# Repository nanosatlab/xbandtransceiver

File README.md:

# **Description**

The subsystem is designed as a generic X-band front-end subsystem. It will have to communicate with an On-Board-Computer (OBC) using UART protocol, be powered from the spacecraft’s 12 V power bus and have a PC/104 daughter board form factor. It also has to ensure a downlink data rate of at least 10 Mbps from 5º over the horizon at a 550 km LEO orbit, and with a bit-error-rate (BER) of 10^-5.

The subsystem is formed by:	SDR <-> Front-End <-> Antenna

The objective of this repository is to make accessible all the files related to the X-band transceiver, also called XCOMMS, which includes the hardware designs and all the necessary software of the subsystem as well as the different test boards that have been developed. This repository also includes the design of the required evaluatino boards that have been required for testing the subsystem.

# **Current state of the project**

At the moment, none of the PCB designs have been updated because they are pending to be translated from Altium to KiCad.
The project just includes the Front-End part.
The SDR and antenna parts are TBD. 

# **Project Tree Structure**

	XCOMMS
	├───Readme
	├───FrontEnd
	│   ├───Readme
	│   ├───HW
	│   │   ├───KiCad_Libraries
	│   │   ├───XCOMMS_Interface
	│   │   └───XCOMMS_RF
	│   └───SW
 	│	
	└───TesBoards
	    ├───PA_HMC952ALP5GE
	    │   ├───HW
	    │   └───SW
	    └───PLL_LMX2572
	    	├───Readme
		├───HW
		└───SW
		    ├───LMX2572
		    └───LMX2572_TICSPRO

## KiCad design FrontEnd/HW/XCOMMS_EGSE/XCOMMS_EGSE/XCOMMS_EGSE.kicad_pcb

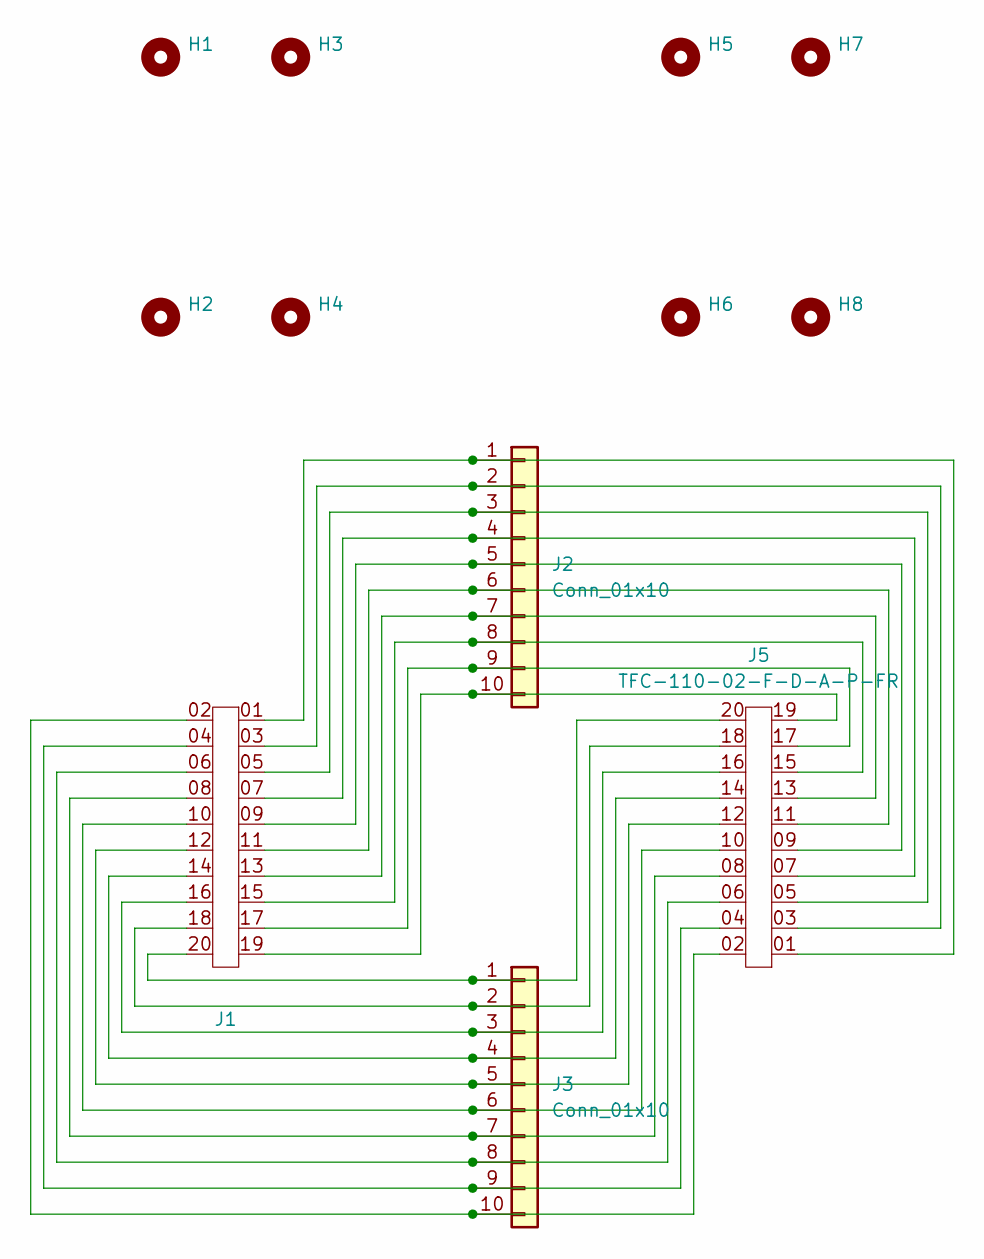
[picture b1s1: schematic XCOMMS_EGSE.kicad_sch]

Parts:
H1, H2, H3, H4, H5, H6, H7, H8: MountingHole; MountingHole_2.7mm_M2.5
J1: TFC-110-02-F-D-A-P-FR; SAMTEC_TFC-110-02-F-D-A-P-FR
J2, J3: Conn_01x10; PinSocket_1x10_P2.54mm_Vertical
J5: TFC-110-02-F-D-A-P-FR; SAMTEC_SFC-110-T2-F-D-A-TR

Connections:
unnamed: J1.01, J2.1, J5.01
unnamed: J1.02, J3.10, J5.02
unnamed: J1.03, J2.2, J5.03
unnamed: J1.04, J3.9, J5.04
unnamed: J1.05, J2.3, J5.05
unnamed: J1.06, J3.8, J5.06
unnamed: J1.07, J2.4, J5.07
unnamed: J1.08, J3.7, J5.08
unnamed: J1.09, J2.5, J5.09
unnamed: J1.10, J3.6, J5.10
unnamed: J1.11, J2.6, J5.11
unnamed: J1.12, J3.5, J5.12
unnamed: J1.13, J2.7, J5.13
unnamed: J1.14, J3.4, J5.14
unnamed: J1.15, J2.8, J5.15
unnamed: J1.16, J3.3, J5.16
unnamed: J1.17, J2.9, J5.17
unnamed: J1.18, J3.2, J5.18
unnamed: J1.19, J2.10, J5.19
unnamed: J1.20, J3.1, J5.20

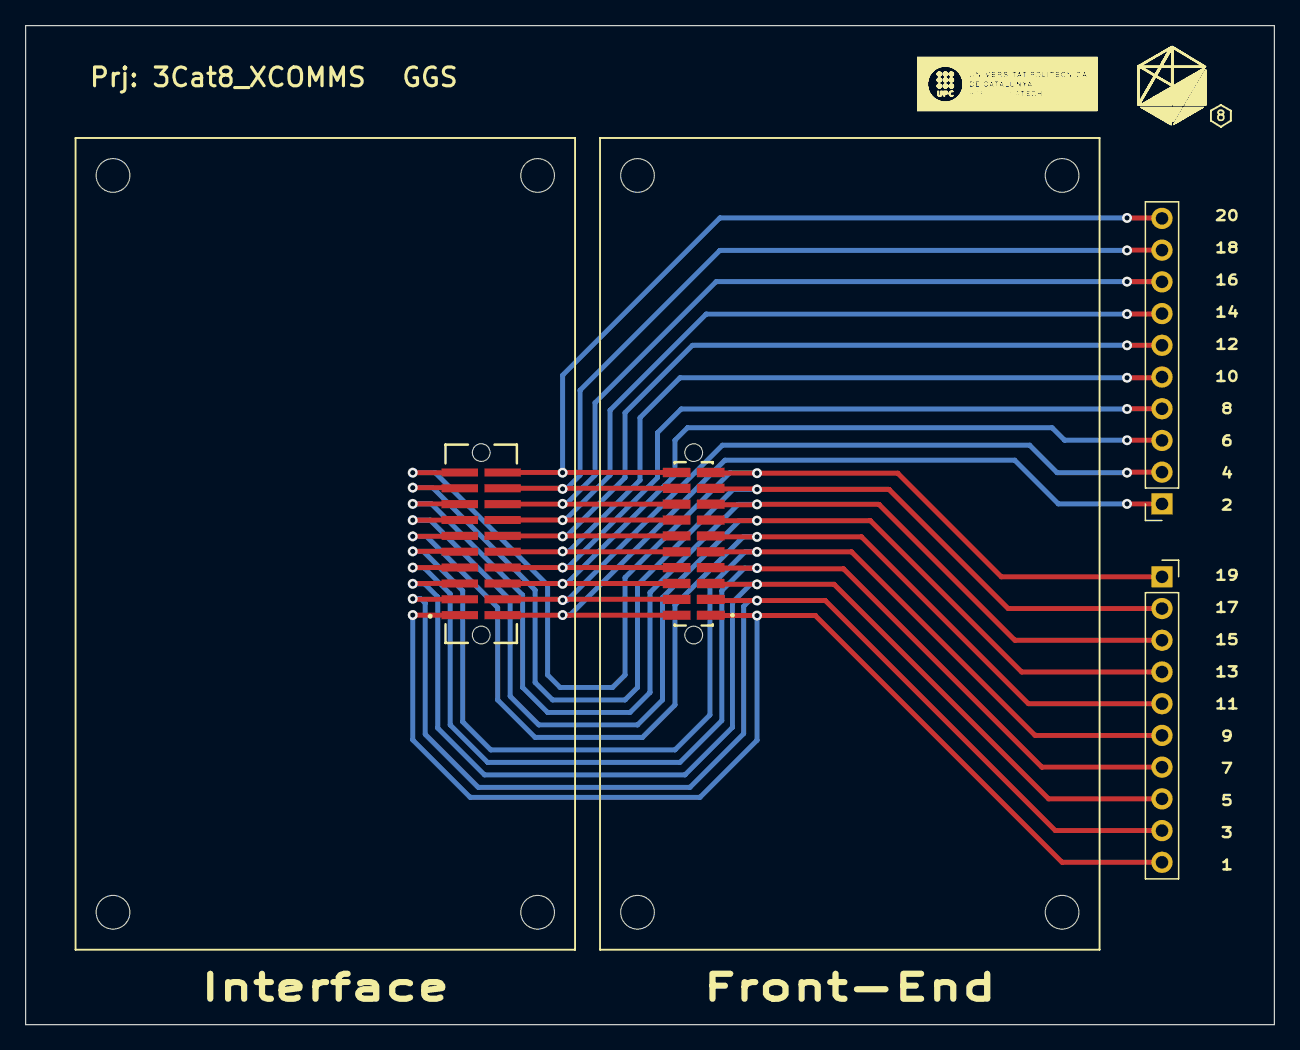
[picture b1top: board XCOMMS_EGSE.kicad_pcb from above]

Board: 2 copper layers, 100.0 x 80.0 mm, 12 parts (0 on the bottom side), 20 nets.

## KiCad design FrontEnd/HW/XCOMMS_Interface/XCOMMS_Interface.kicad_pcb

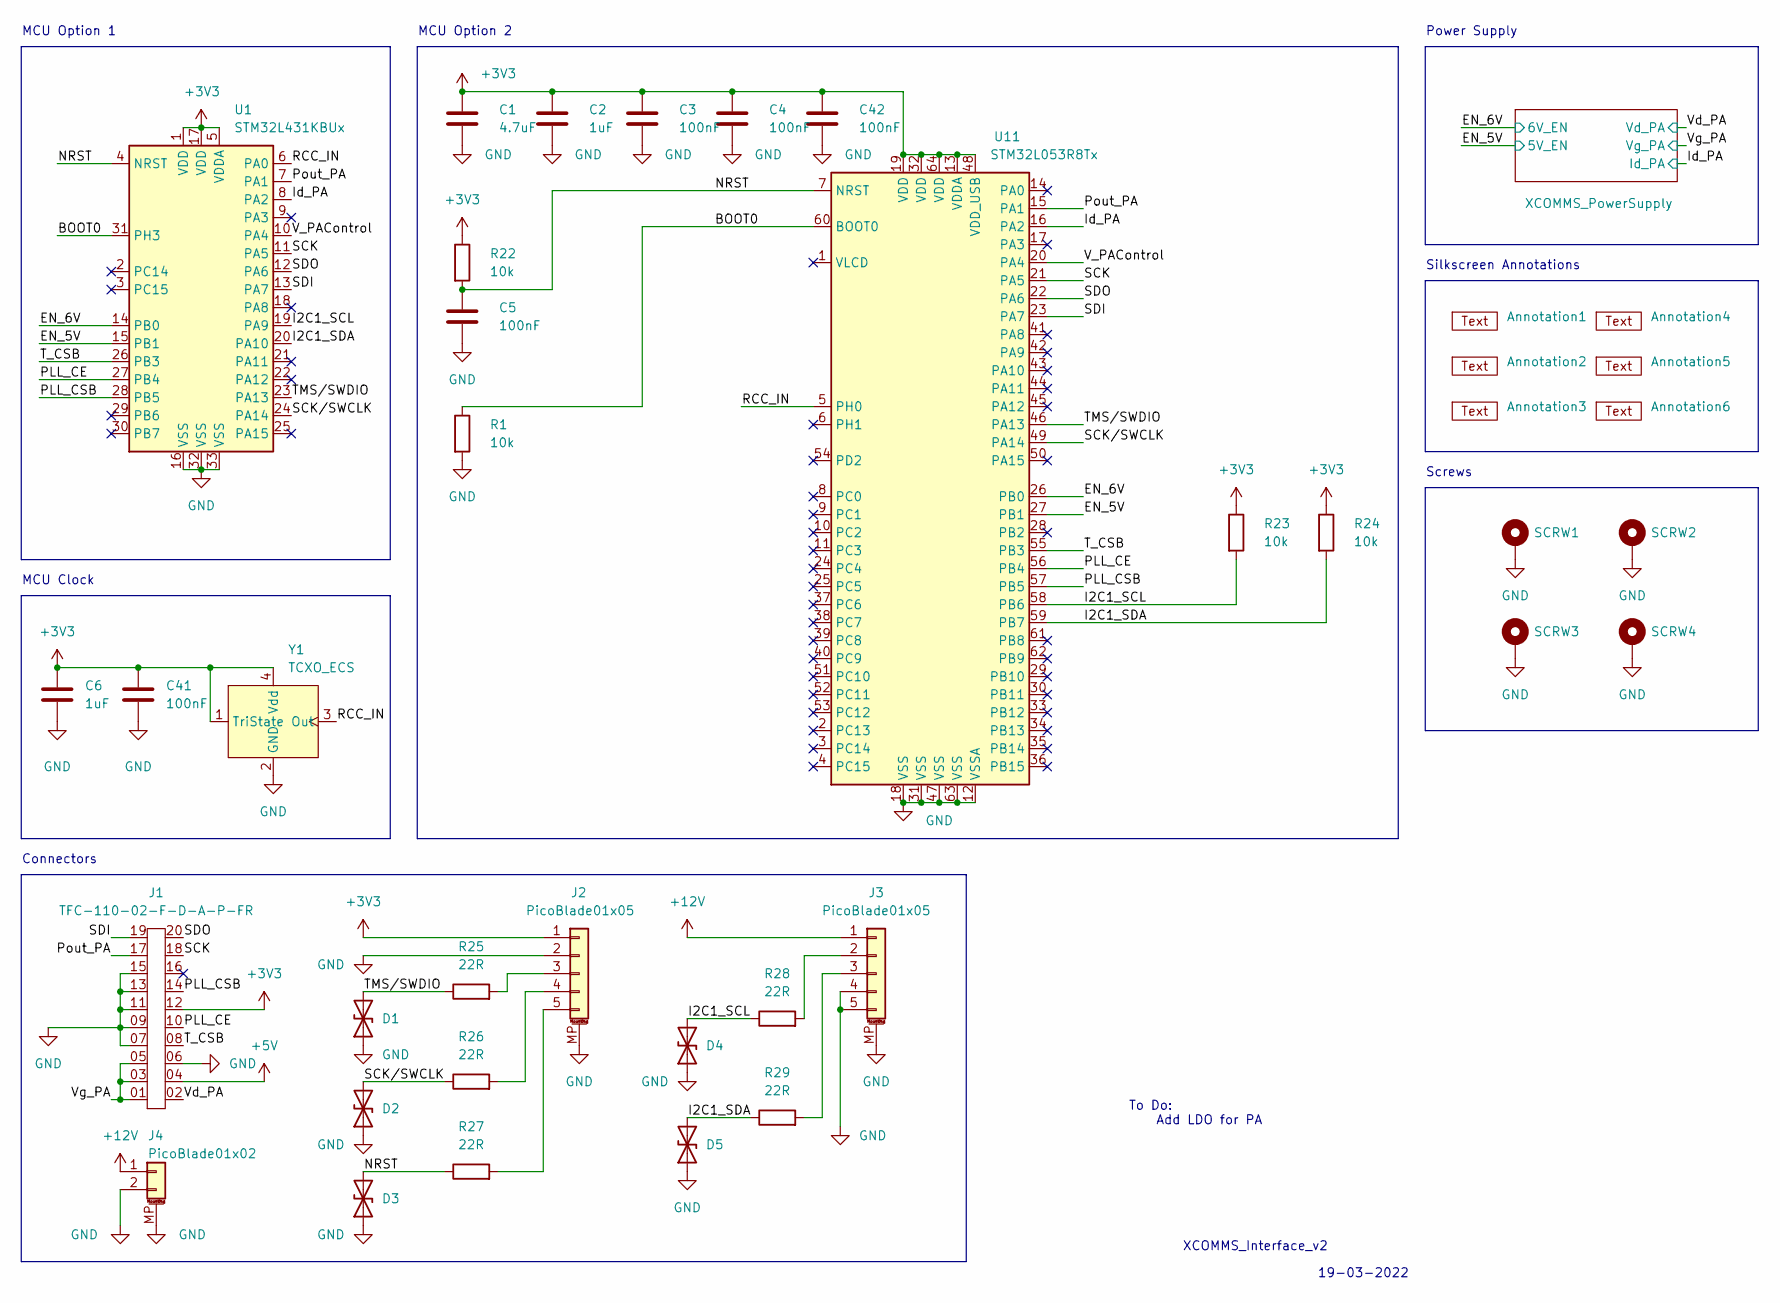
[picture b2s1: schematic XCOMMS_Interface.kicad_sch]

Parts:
Annotation1: Silkscreen_Annotation; Bike
Annotation2: Silkscreen_Annotation; GGS
Annotation3: Silkscreen_Annotation; NSL
Annotation4: Silkscreen_Annotation; Prj
Annotation5: Silkscreen_Annotation; Rev
Annotation6: Silkscreen_Annotation; UPC
C1: 4.7uF; C_0603_1608Metric
C2, C6: 1uF; C_0603_1608Metric
C3, C4, C5, C41, C42: 100nF; C_0603_1608Metric
D1, D2, D3, D4, D5: SZESD9X3.3ST5G; D_SOD-923; MPN SZESD9X3.3ST5G
J1: TFC-110-02-F-D-A-P-FR; SAMTEC_TFC-110-02-F-D-A-P-FR
J2, J3: PicoBlade01x05; Molex_PicoBlade_53261-0571_1x05-1MP_P1.25mm_Horizontal
J4: PicoBlade01x02; Molex_PicoBlade_53261-0271_1x02-1MP_P1.25mm_Horizontal
R1, R22, R23, R24: 10k; R_0603_1608Metric
R25, R26, R27, R28, R29: 22R; R_0603_1608Metric
SCRW1, SCRW2, SCRW3, SCRW4: MountingHole_Pad; MountingHole_2.7mm_M2.5_Pad
U1: STM32L431KBUx; QFN-32-1EP_5x5mm_P0.5mm_EP3.45x3.45mm
U11: STM32L053R8Tx; LQFP-64_10x10mm_P0.5mm
Y1: TCXO_ECS

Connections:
+3V3: C1.1, C2.1, C3.1, C4.1, C6.1, C41.1, C42.1, J1.12, J2.1, R22.1, R23.1, R24.1, U1.1 (VDD), U1.5 (VDDA), U1.17 (VDD), U11.13 (VDDA), U11.19 (VDD), U11.32 (VDD), U11.48 (VDD_USB), U11.64 (VDD), Y1.1 (TriState), Y1.4 (Vdd); also elsewhere on the board
+5V: J1.04; also elsewhere on the board
+12V: J3.1, J4.1; also elsewhere on the board
/BOOT0: R1.1, U1.31 (PH3), U11.60 (BOOT0)
/EN_5V: U1.15 (PB1), U11.27 (PB1); also elsewhere on the board
/EN_6V: U1.14 (PB0), U11.26 (PB0); also elsewhere on the board
/I2C1_SCL: D4.2 (A2), R23.2, R28.1, U1.19 (PA9), U11.58 (PB6)
/I2C1_SDA: D5.2 (A2), R24.2, R29.1, U1.20 (PA10), U11.59 (PB7)
/Id_PA: U1.8 (PA2), U11.16 (PA2); also elsewhere on the board
/NRST: C5.1, D3.2 (A2), R22.2, R27.1, U1.4 (NRST), U11.7 (NRST)
/PLL_CE: J1.10, U1.27 (PB4), U11.56 (PB4)
/PLL_CSB: J1.14, U1.28 (PB5), U11.57 (PB5)
/Pout_PA: J1.17, U1.7 (PA1), U11.15 (PA1)
/RCC_IN: U1.6 (PA0), U11.5 (PH0), Y1.3 (Out)
/SCK: J1.18, U1.11 (PA5), U11.21 (PA5)
/SCK/SWCLK: D2.2 (A2), R26.1, U1.24 (PA14), U11.49 (PA14)
/SDI: J1.19, U1.13 (PA7), U11.23 (PA7)
/SDO: J1.20, U1.12 (PA6), U11.22 (PA6)
/TMS/SWDIO: D1.2 (A2), R25.1, U1.23 (PA13), U11.46 (PA13)
/T_CSB: J1.08, U1.26 (PB3), U11.55 (PB3)
/V_PAControl: U1.10 (PA4), U11.20 (PA4)
/Vd_PA: J1.02; also elsewhere on the board
/Vg_PA: J1.01, J1.03, J1.05; also elsewhere on the board
GND: C1.2, C2.2, C3.2, C4.2, C5.2, C6.2, C41.2, C42.2, D1.1 (A1), D2.1 (A1), D3.1 (A1), D4.1 (A1), D5.1 (A1), J1.06, J1.07, J1.09, J1.11, J1.13, J1.15, J2.2, J2.MP (MountPin), J3.4, J3.5, J3.MP (MountPin), J4.2, J4.MP (MountPin), R1.2, SCRW1.1, SCRW2.1, SCRW3.1, SCRW4.1, U1.16 (VSS), U1.32 (VSS), U1.33 (VSS), U11.12 (VSSA), U11.18 (VSS), U11.31 (VSS), U11.47 (VSS), U11.63 (VSS), Y1.2 (GND); also elsewhere on the board
unnamed: J2.3, R25.2
unnamed: J2.4, R26.2
unnamed: J2.5, R27.2
unnamed: J3.2, R28.2
unnamed: J3.3, R29.2

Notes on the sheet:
Silkscreen Annotations
MCU Option 2
Power Supply
MCU Clock
MCU Option 1
XCOMMS_Interface_v2
Connectors
19-03-2022
Screws
To Do: Add LDO for PA

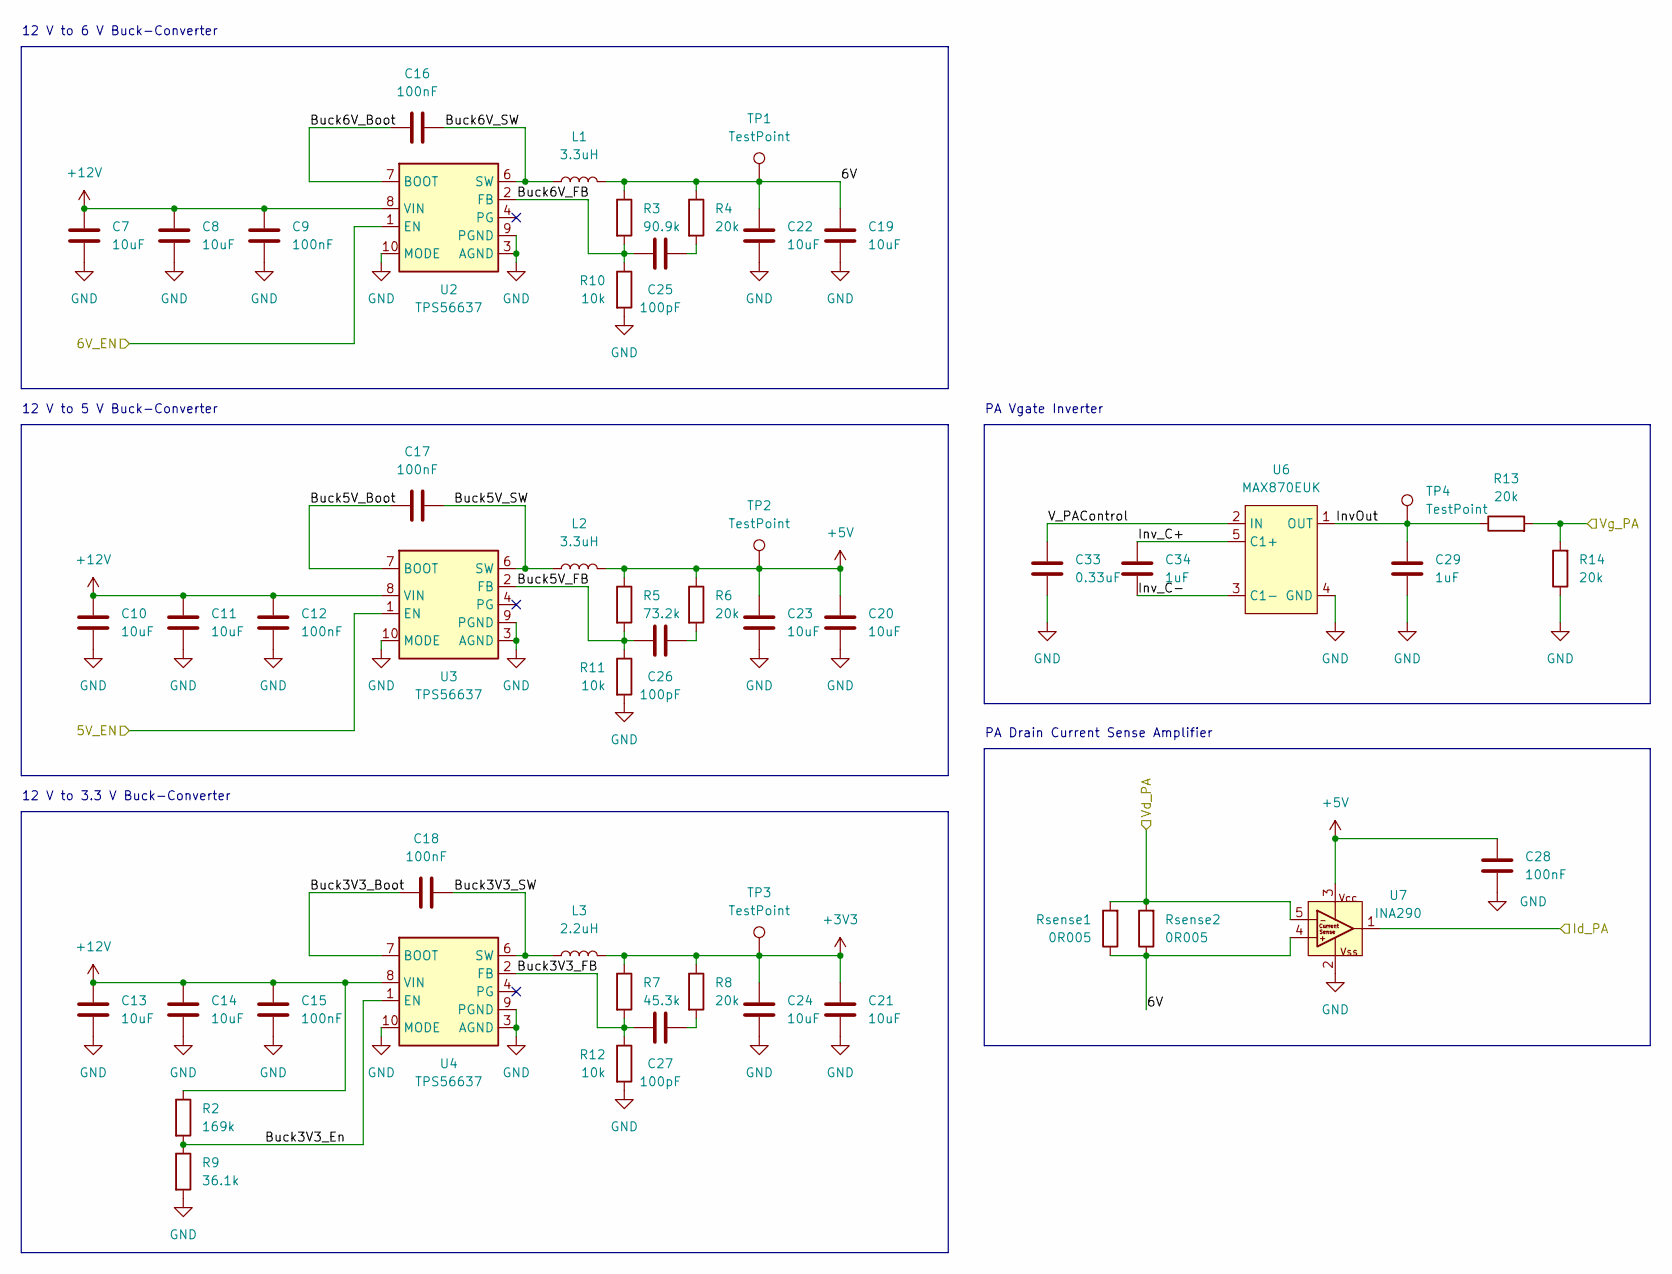
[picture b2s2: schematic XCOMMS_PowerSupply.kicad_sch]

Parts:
C7, C8, C10, C11, C13, C14, C19, C20, C21, C22, C23, C24: 10uF; C_0603_1608Metric
C9, C12, C15, C16, C17, C18, C28: 100nF; C_0603_1608Metric
C25, C26, C27: 100pF; C_0603_1608Metric
C29, C34: 1uF; C_0603_1608Metric
C33: 0.33uF; C_0603_1608Metric
L1, L2: 3.3uH; L_Bourns_SRP5030T
L3: 2.2uH; L_Coilcraft_XAL60xx_6.36x6.56mm
R2: 169k; R_0603_1608Metric
R3: 90.9k; R_0603_1608Metric
R4, R6, R8, R13, R14: 20k; R_0603_1608Metric
R5: 73.2k; R_0603_1608Metric
R7: 45.3k; R_0603_1608Metric
R9: 36.1k; R_0603_1608Metric
R10, R11, R12: 10k; R_0603_1608Metric
Rsense1, Rsense2: 0R005; R_1206_3216Metric
TP1, TP2, TP3, TP4: TestPoint; TestPoint_Pad_D1.0mm
U2, U3, U4: TPS56637; TPS56637RPAR
U6: MAX870EUK; SOT-23-5
U7: INA290; SC70-5

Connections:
+3V3: C21.1, C24.1, L3.2, R7.1, R8.1, TP3.1; also elsewhere on the board
+5V: C20.1, C23.1, C28.2, L2.2, R5.1, R6.1, TP2.1, U7.3 (VCC); also elsewhere on the board
+12V: C7.1, C8.1, C9.1, C10.1, C11.1, C12.1, C13.1, C14.1, C15.1, R2.1, U2.8 (VIN), U3.8 (VIN), U4.8 (VIN); also elsewhere on the board
/EN_5V: U3.1 (EN); also elsewhere on the board
/EN_6V: U2.1 (EN); also elsewhere on the board
/Id_PA: U7.1 (OUT); also elsewhere on the board
/Vd_PA: Rsense1.2, Rsense2.2, U7.5 (IN-); also elsewhere on the board
/Vg_PA: R13.2, R14.2; also elsewhere on the board
/XCOMMS_PowerSupply/6V: C19.1, C22.1, L1.2, R3.1, R4.1, Rsense1.1, Rsense2.1, TP1.1, U7.4 (IN+)
/XCOMMS_PowerSupply/Buck3V3_Boot: C18.1, U4.7 (BOOT)
/XCOMMS_PowerSupply/Buck3V3_En: R2.2, R9.1, U4.1 (EN)
/XCOMMS_PowerSupply/Buck3V3_FB: C27.1, R7.2, R12.1, U4.2 (FB)
/XCOMMS_PowerSupply/Buck3V3_SW: C18.2, L3.1, U4.6 (SW)
/XCOMMS_PowerSupply/Buck5V_Boot: C17.1, U3.7 (BOOT)
/XCOMMS_PowerSupply/Buck5V_FB: C26.1, R5.2, R11.1, U3.2 (FB)
/XCOMMS_PowerSupply/Buck5V_SW: C17.2, L2.1, U3.6 (SW)
/XCOMMS_PowerSupply/Buck6V_Boot: C16.1, U2.7 (BOOT)
/XCOMMS_PowerSupply/Buck6V_FB: C25.1, R3.2, R10.1, U2.2 (FB)
/XCOMMS_PowerSupply/Buck6V_SW: C16.2, L1.1, U2.6 (SW)
/XCOMMS_PowerSupply/InvOut: C29.2, R13.1, TP4.1, U6.1 (OUT)
/XCOMMS_PowerSupply/Inv_C+: C34.2, U6.5 (C1+)
/XCOMMS_PowerSupply/Inv_C-: C34.1, U6.3 (C1-)
/XCOMMS_PowerSupply/V_PAControl: C33.2, U6.2 (IN)
GND: C7.2, C8.2, C9.2, C10.2, C11.2, C12.2, C13.2, C14.2, C15.2, C19.2, C20.2, C21.2, C22.2, C23.2, C24.2, C28.1, C29.1, C33.1, R9.2, R10.2, R11.2, R12.2, R14.1, U2.3 (AGND), U2.9 (PGND), U2.10 (MODE), U3.3 (AGND), U3.9 (PGND), U3.10 (MODE), U4.3 (AGND), U4.9 (PGND), U4.10 (MODE), U6.4 (GND), U7.2 (VSS); also elsewhere on the board
unnamed: C25.2, R4.2
unnamed: C26.2, R6.2
unnamed: C27.2, R8.2

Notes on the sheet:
12 V to 6 V Buck-Converter
12 V to 3.3 V Buck-Converter
PA Vgate Inverter
12 V to 5 V Buck-Converter
PA Drain Current Sense Amplifier

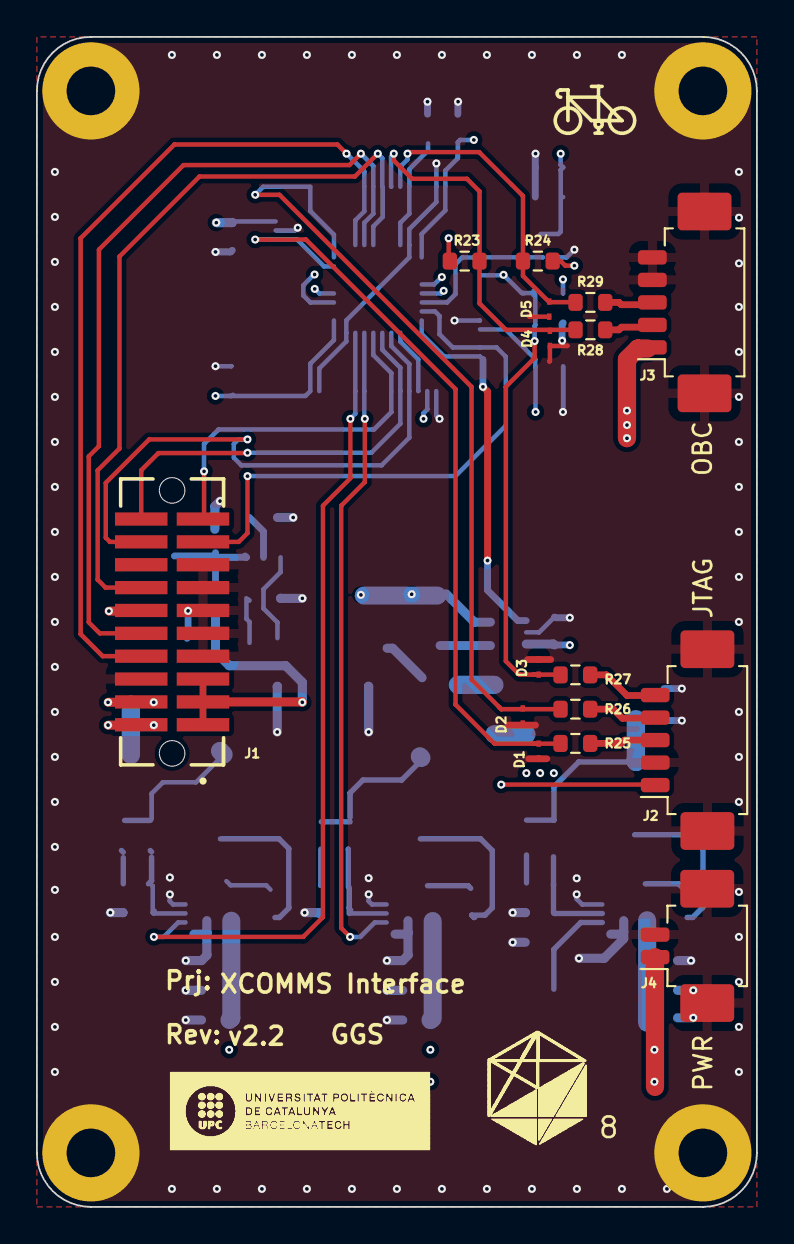
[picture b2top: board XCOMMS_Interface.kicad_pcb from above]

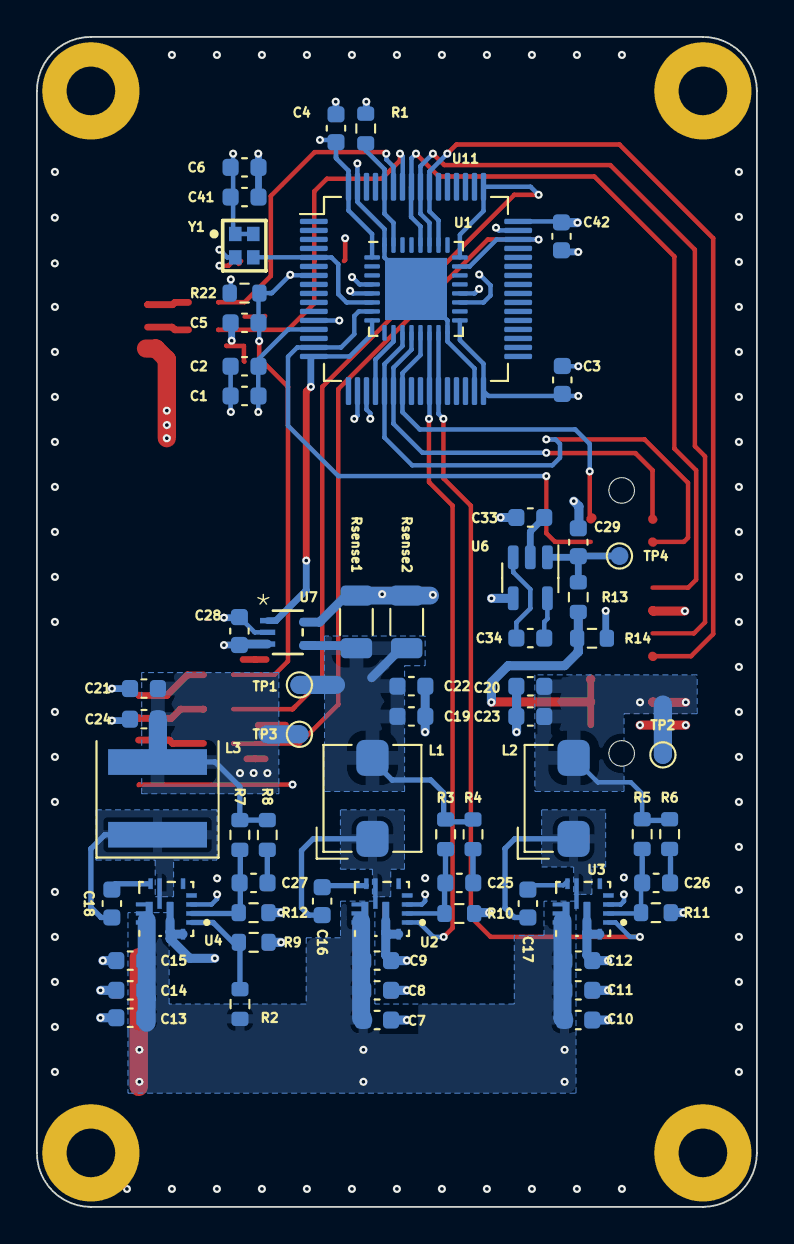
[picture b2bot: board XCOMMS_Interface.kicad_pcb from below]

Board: 4 copper layers, 40.0 x 65.0 mm, 91 parts (65 on the bottom side), 47 nets.

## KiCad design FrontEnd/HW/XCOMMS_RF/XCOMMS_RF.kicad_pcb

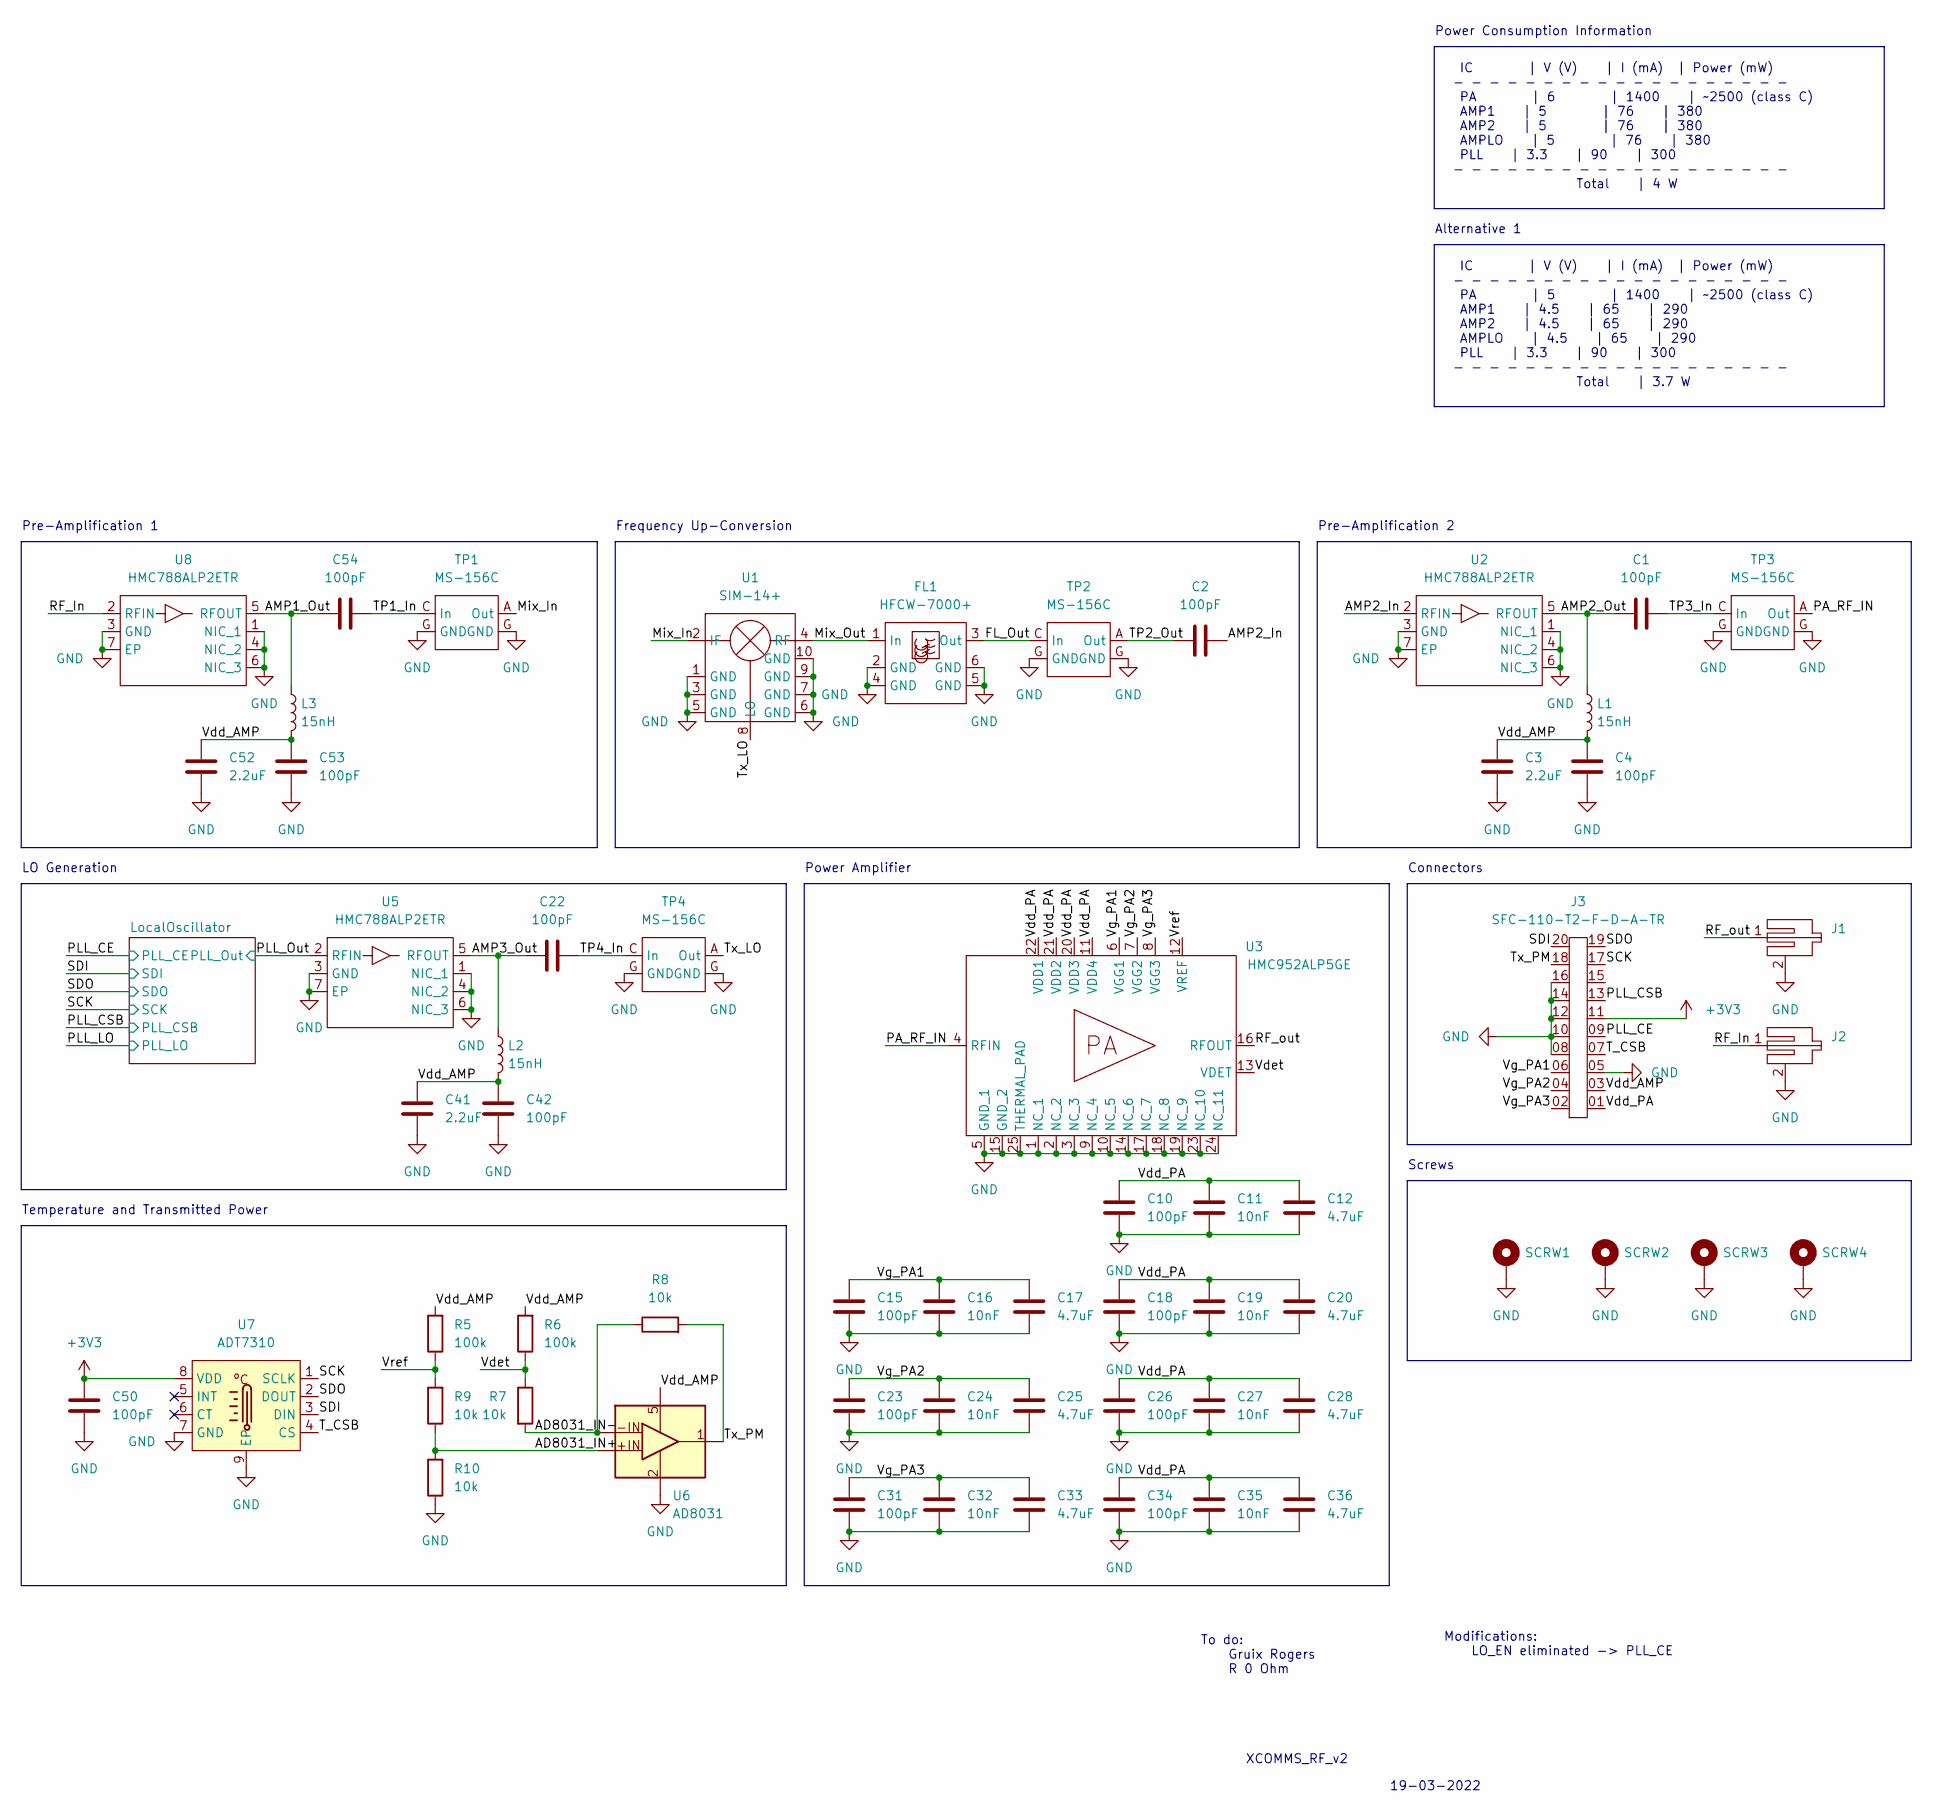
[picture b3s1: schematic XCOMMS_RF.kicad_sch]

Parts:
C1, C2, C4, C10, C15, C18, C22, C23, C26, C31, C34, C42, C50, C53, C54: 100pF; C_0402_1005Metric
C3, C41, C52: 2.2uF; C_0603_1608Metric
C11, C16, C19, C24, C27, C32, C35: 10nF; C_0603_1608Metric
C12, C17, C20, C25, C28, C33, C36: 4.7uF; C_0603_1608Metric
FL1: HFCW-7000+; JC0603C
J1, J2: SMP-MSLD-PCE-5T
J3: SFC-110-T2-F-D-A-TR; SAMTEC_SFC-110-T2-F-D-A-TR
L1, L2, L3: 15nH; L_0603_1608Metric
R5, R6: 100k; R_0603_1608Metric
R7, R8, R9, R10: 10k; R_0603_1608Metric
SCRW1, SCRW2, SCRW3, SCRW4: MountingHole_Pad; MountingHole_2.7mm_M2.5_ISO14580_Pad
TP1, TP2, TP3, TP4: MS-156C; CoaxialSwitch_Hirose_MS-156C3_Horizontal
U1: SIM-14+; SIM24MH
U2, U5, U8: HMC788ALP2ETR; SON65P200X200X90-7N-D; Mouser Part Number 584-HMC788ALP2ETR
U3: HMC952ALP5GE; QFN65P500X500X100-25N-D; Mouser Part Number 584-HMC952ALP5GE
U6: AD8031; SOT-23-5; MANUFACTURER_PART_NUMBER AD8031ARTZ-REEL7
U7: ADT7310; SOIC-8-1EP_3.9x4.9mm_P1.27mm_EP2.41x3.81mm

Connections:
+3V3: C50.2, J3.11, U7.8 (VDD); also elsewhere on the board
/AD8031_IN+: R9.1, R10.2, U6.3 (+IN)
/AD8031_IN-: R7.2, R8.1, U6.4 (-IN)
/AMP1_Out: C54.1, L3.1, U8.5 (RFOUT)
/AMP2_In: C2.2, U2.2 (RFIN)
/AMP2_Out: C1.1, L1.1, U2.5 (RFOUT)
/AMP3_Out: C22.1, L2.1, U5.5 (RFOUT)
/FL_Out: FL1.3 (Out), TP2.C (In)
/Mix_In: TP1.A (Out), U1.2 (IF)
/Mix_Out: FL1.1 (In), U1.4 (RF)
/PA_RF_IN: TP3.A (Out), U3.4 (RFIN)
/PLL_CE: J3.09; also elsewhere on the board
/PLL_CSB: J3.13; also elsewhere on the board
/PLL_Out: U5.2 (RFIN); also elsewhere on the board
/RF_In: J2.1, U8.2 (RFIN)
/RF_out: J1.1, U3.16 (RFOUT)
/SCK: J3.17, U7.1 (SCLK); also elsewhere on the board
/SDI: J3.20, U7.3 (DIN); also elsewhere on the board
/SDO: J3.19, U7.2 (DOUT); also elsewhere on the board
/TP1_In: C54.2, TP1.C (In)
/TP2_Out: C2.1, TP2.A (Out)
/TP3_In: C1.2, TP3.C (In)
/TP4_In: C22.2, TP4.C (In)
/T_CSB: J3.07, U7.4 (CS)
/Tx_LO: TP4.A (Out), U1.8 (LO)
/Tx_PM: J3.18, R8.2, U6.1 (VOUT)
/Vdd_AMP: C3.2, C4.2, C41.2, C42.2, C52.2, C53.2, J3.03, L1.2, L2.2, L3.2, R5.2, R6.2, U6.5 (+VS)
/Vdd_PA: C10.2, C11.2, C12.2, C18.2, C19.2, C20.2, C26.2, C27.2, C28.2, C34.2, C35.2, C36.2, J3.01, U3.11 (VDD4), U3.20 (VDD3), U3.21 (VDD2), U3.22 (VDD1)
/Vdet: R6.1, R7.1, U3.13 (VDET)
/Vg_PA1: C15.2, C16.2, C17.2, J3.06, U3.6 (VGG1)
/Vg_PA2: C23.2, C24.2, C25.2, J3.04, U3.7 (VGG2)
/Vg_PA3: C31.2, C32.2, C33.2, J3.02, U3.8 (VGG3)
/Vref: R5.1, R9.2, U3.12 (VREF)
GND: C3.1, C4.1, C10.1, C11.1, C12.1, C15.1, C16.1, C17.1, C18.1, C19.1, C20.1, C23.1, C24.1, C25.1, C26.1, C27.1, C28.1, C31.1, C32.1, C33.1, C34.1, C35.1, C36.1, C41.1, C42.1, C50.1, C52.1, C53.1, FL1.2 (GND), FL1.4 (GND), FL1.5 (GND), FL1.6 (GND), J1.2, J2.2, J3.05, J3.08, J3.10, J3.12, J3.14, J3.16, R10.1, SCRW1.1, SCRW2.1, SCRW3.1, SCRW4.1, TP1.G (GND), TP2.G (GND), TP3.G (GND), TP4.G (GND), U1.1 (GND), U1.3 (GND), U1.5 (GND), U1.6 (GND), U1.7 (GND), U1.9 (GND), U1.10 (GND), U2.1 (NIC_1), U2.3 (GND), U2.4 (NIC_2), U2.6 (NIC_3), U2.7 (EP), U3.1 (NC_1), U3.2 (NC_2), U3.3 (NC_3), U3.5 (GND_1), U3.9 (NC_4), U3.10 (NC_5), U3.14 (NC_6), U3.15 (GND_2), U3.17 (NC_7), U3.18 (NC_8), U3.19 (NC_9), U3.23 (NC_10), U3.24 (NC_11), U3.25 (THERMAL_PAD), U5.1 (NIC_1), U5.3 (GND), U5.4 (NIC_2), U5.6 (NIC_3), U5.7 (EP), U6.2 (-VS), U7.7 (GND), U7.9 (EP), U8.1 (NIC_1), U8.3 (GND), U8.4 (NIC_2), U8.6 (NIC_3), U8.7 (EP); also elsewhere on the board

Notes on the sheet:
LO Generation
Temperature and Transmitted Power
Power Amplifier
IC | V (V) | I (mA) | Power (mW) - - - - - - - - - - - - - - - - - - - PA | 6 | 1400 | ~2500 (class C) AMP1 | 5 | 76 | 380 AMP2 | 5 | 76 | 380 AMPLO | 5 | 76 | 380 PLL | 3.3 | 90 | 300 - - - - - - - - - - - - - - - - - - - Total | 4 W
Alternative 1
Screws
19-03-2022
Frequency Up-Conversion
XCOMMS_RF_v2
Connectors
Pre-Amplification 1
To do: Gruix Rogers R 0 Ohm
Pre-Amplification 2
Modifications: LO_EN eliminated -> PLL_CE
IC | V (V) | I (mA) | Power (mW) - - - - - - - - - - - - - - - - - - - PA | 5 | 1400 | ~2500 (class C) AMP1 | 4.5 | 65 | 290 AMP2 | 4.5 | 65 | 290 AMPLO | 4.5 | 65 | 290 PLL | 3.3 | 90 | 300 - - - - - - - - - - - - - - - - - - - Total | 3.7 W
Power Consumption Information

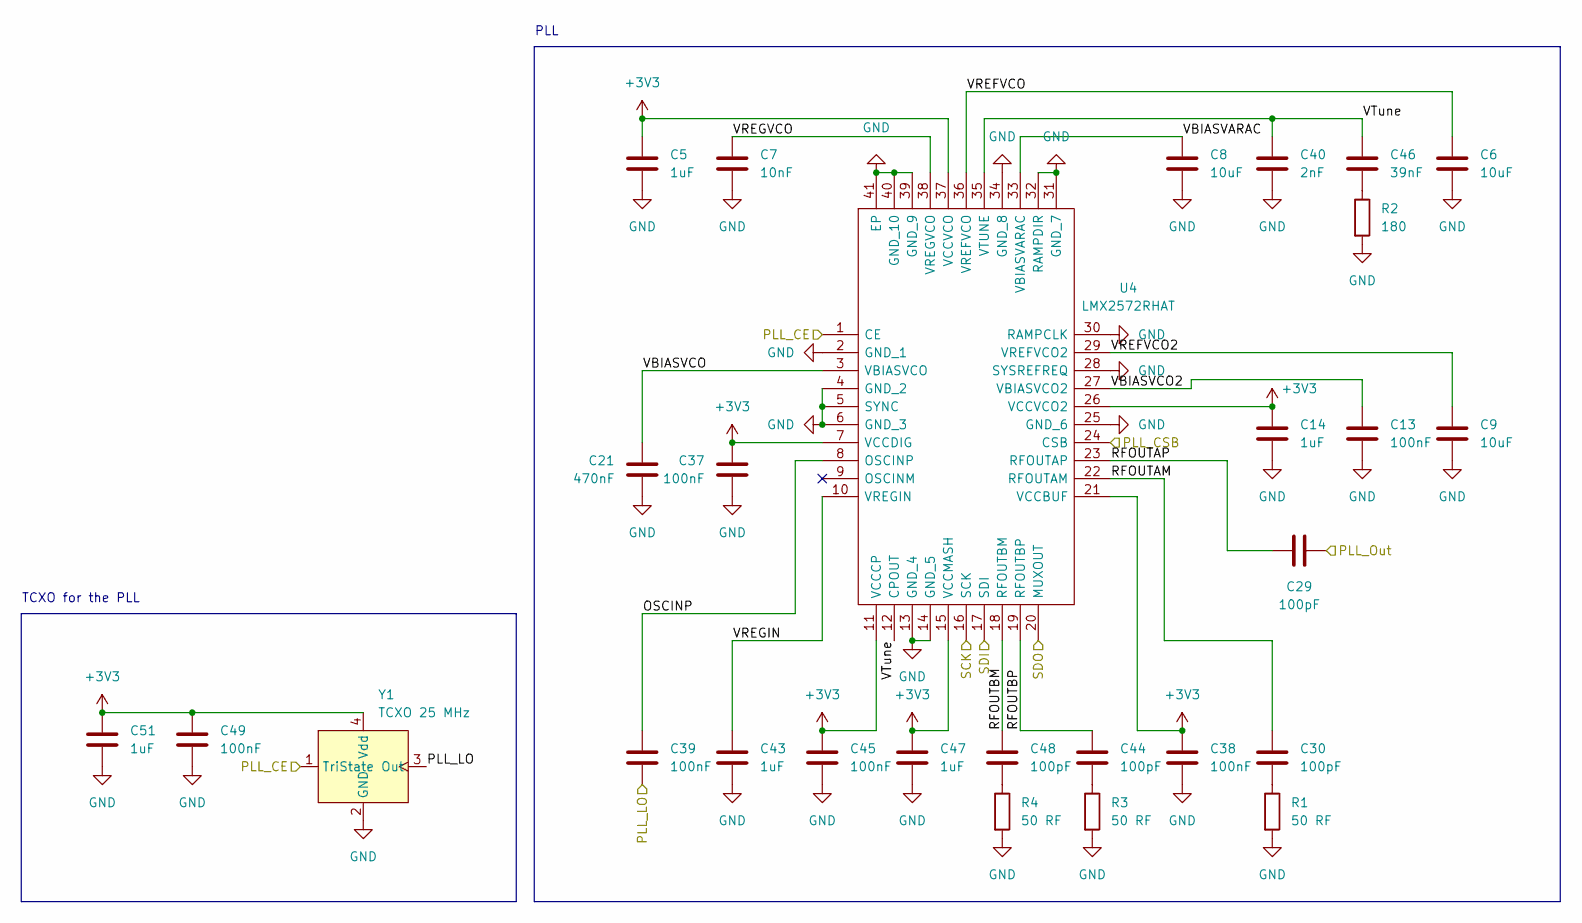
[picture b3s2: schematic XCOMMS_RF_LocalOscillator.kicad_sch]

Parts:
C5, C14, C43, C47, C51: 1uF; C_0603_1608Metric
C6, C8, C9: 10uF; C_0603_1608Metric
C7: 10nF; C_0603_1608Metric
C13, C37, C38, C39, C45, C49: 100nF; C_0603_1608Metric
C21: 470nF; C_0603_1608Metric
C29, C30, C44, C48: 100pF; C_0402_1005Metric
C40: 2nF; C_0603_1608Metric
C46: 39nF; C_0603_1608Metric
R1, R3, R4: 50 RF; R_0402_1005Metric
R2: 180; R_0603_1608Metric
U4: LMX2572RHAT; QFN50P600X600X100-41N-D; Mouser Part Number 595-LMX2572RHAT
Y1: TCXO 25 MHz; TCXO_ECS

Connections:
+3V3: C5.2, C14.2, C37.2, C38.2, C45.2, C47.2, C49.1, C51.2, U4.7 (VCCDIG), U4.11 (VCCCP), U4.15 (VCCMASH), U4.21 (VCCBUF), U4.26 (VCCVCO2), U4.37 (VCCVCO), Y1.4 (Vdd); also elsewhere on the board
/LocalOscillator/OSCINP: C39.2, U4.8 (OSCINP)
/LocalOscillator/RFOUTAM: C30.2, U4.22 (RFOUTAM)
/LocalOscillator/RFOUTAP: C29.1, U4.23 (RFOUTAP)
/LocalOscillator/RFOUTBM: C48.2, U4.18 (RFOUTBM)
/LocalOscillator/RFOUTBP: C44.2, U4.19 (RFOUTBP)
/LocalOscillator/VBIASVARAC: C8.2, U4.33 (VBIASVARAC)
/LocalOscillator/VBIASVCO: C21.2, U4.3 (VBIASVCO)
/LocalOscillator/VBIASVCO2: C13.2, U4.27 (VBIASVCO2)
/LocalOscillator/VREFVCO: C6.2, U4.36 (VREFVCO)
/LocalOscillator/VREFVCO2: C9.2, U4.29 (VREFVCO2)
/LocalOscillator/VREGIN: C43.2, U4.10 (VREGIN)
/LocalOscillator/VREGVCO: C7.2, U4.38 (VREGVCO)
/LocalOscillator/VTune: C40.2, C46.2, U4.12 (CPOUT), U4.35 (VTUNE)
/PLL_CE: U4.1 (CE), Y1.1 (TriState); also elsewhere on the board
/PLL_CSB: U4.24 (CSB); also elsewhere on the board
/PLL_LO: C39.1, Y1.3 (Out)
/PLL_Out: C29.2; also elsewhere on the board
/SCK: U4.16 (SCK); also elsewhere on the board
/SDI: U4.17 (SDI); also elsewhere on the board
/SDO: U4.20 (MUXOUT); also elsewhere on the board
GND: C5.1, C6.1, C7.1, C8.1, C9.1, C13.1, C14.1, C21.1, C37.1, C38.1, C40.1, C43.1, C45.1, C47.1, C49.2, C51.1, R1.2, R2.2, R3.2, R4.2, U4.2 (GND_1), U4.4 (GND_2), U4.5 (SYNC), U4.6 (GND_3), U4.13 (GND_4), U4.14 (GND_5), U4.25 (GND_6), U4.28 (SYSREFREQ), U4.30 (RAMPCLK), U4.31 (GND_7), U4.32 (RAMPDIR), U4.34 (GND_8), U4.39 (GND_9), U4.40 (GND_10), U4.41 (EP), Y1.2 (GND); also elsewhere on the board
unnamed: C30.1, R1.1
unnamed: C44.1, R3.1
unnamed: C46.1, R2.1
unnamed: C48.1, R4.1

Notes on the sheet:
TCXO for the PLL
PLL

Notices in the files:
parts and their libraries:
COPYRIGHT: Copyright (C) 2021 Ultra Librarian. All rights reserved.
